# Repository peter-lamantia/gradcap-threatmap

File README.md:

# Graduation Cap Live Threat Map PCB

## About

This is a pet project to learn more about microcontroller development and PCB design.

My plan is to: 
1. Reverse engineer the Fortinet WebSocket API
2. Program an ESP32 to connect to said API and log messages to serial
3. Design a PCB with:
   - an ESP32-S3
   - a world map graphic and WS2812B LEDs placed at key cities
   - a lithium battery and charging circuit
   - dimensions that will place it neatly on a graduation cap
   - a display to show the attack details
4. Program the ESP32 to parse the incoming WebSocket such that:
   - the longitudinal data will map to the closest physical LED on the board
   - the LED will light up with a certain color depending on the threat type
   - ideally, I can make the LEDs animated in a cool way

## Roadmap
- WiFi connection reestablishment
- WebSocket connection reestablishment
- An actual PCB to mess around with. It may be useful to do this in revisions, e.g. make a PCB with the LEDs first, write the software for that, then make a more capable PCB with all components. After all, it is my first time doing this.
- Figure out how to actually debug (not just print program state to serial!)

## Changelog

### 2024-07-07
- Full migration to Platform.io (it's great!)
- Started printing out threats to an OLED display
   - Used the U8g2 library, specifically [u8log](https://github.com/olikraus/u8g2/wiki/u8logreference) for display output
   - Parsed the JSON sent from the WebSocket using [ArduinoJSON](https://arduinojson.org/)
- Added and did some testing with [FastLED](https://github.com/FastLED/FastLED), but have not implemented it yet (it is likely best to wait until I've made the PCB)

### 2024-06-29 (initial commit)
- WiFi connection establishment
- WebSocket connection to Fortinet
- Prints WebSocket messages to serial

## Known issues/fixes
- If serial is enabled, the XIAO ESP32-S3 will not allow reflashing. To fix this, hold the boot button while powering it on, and then flash at will!

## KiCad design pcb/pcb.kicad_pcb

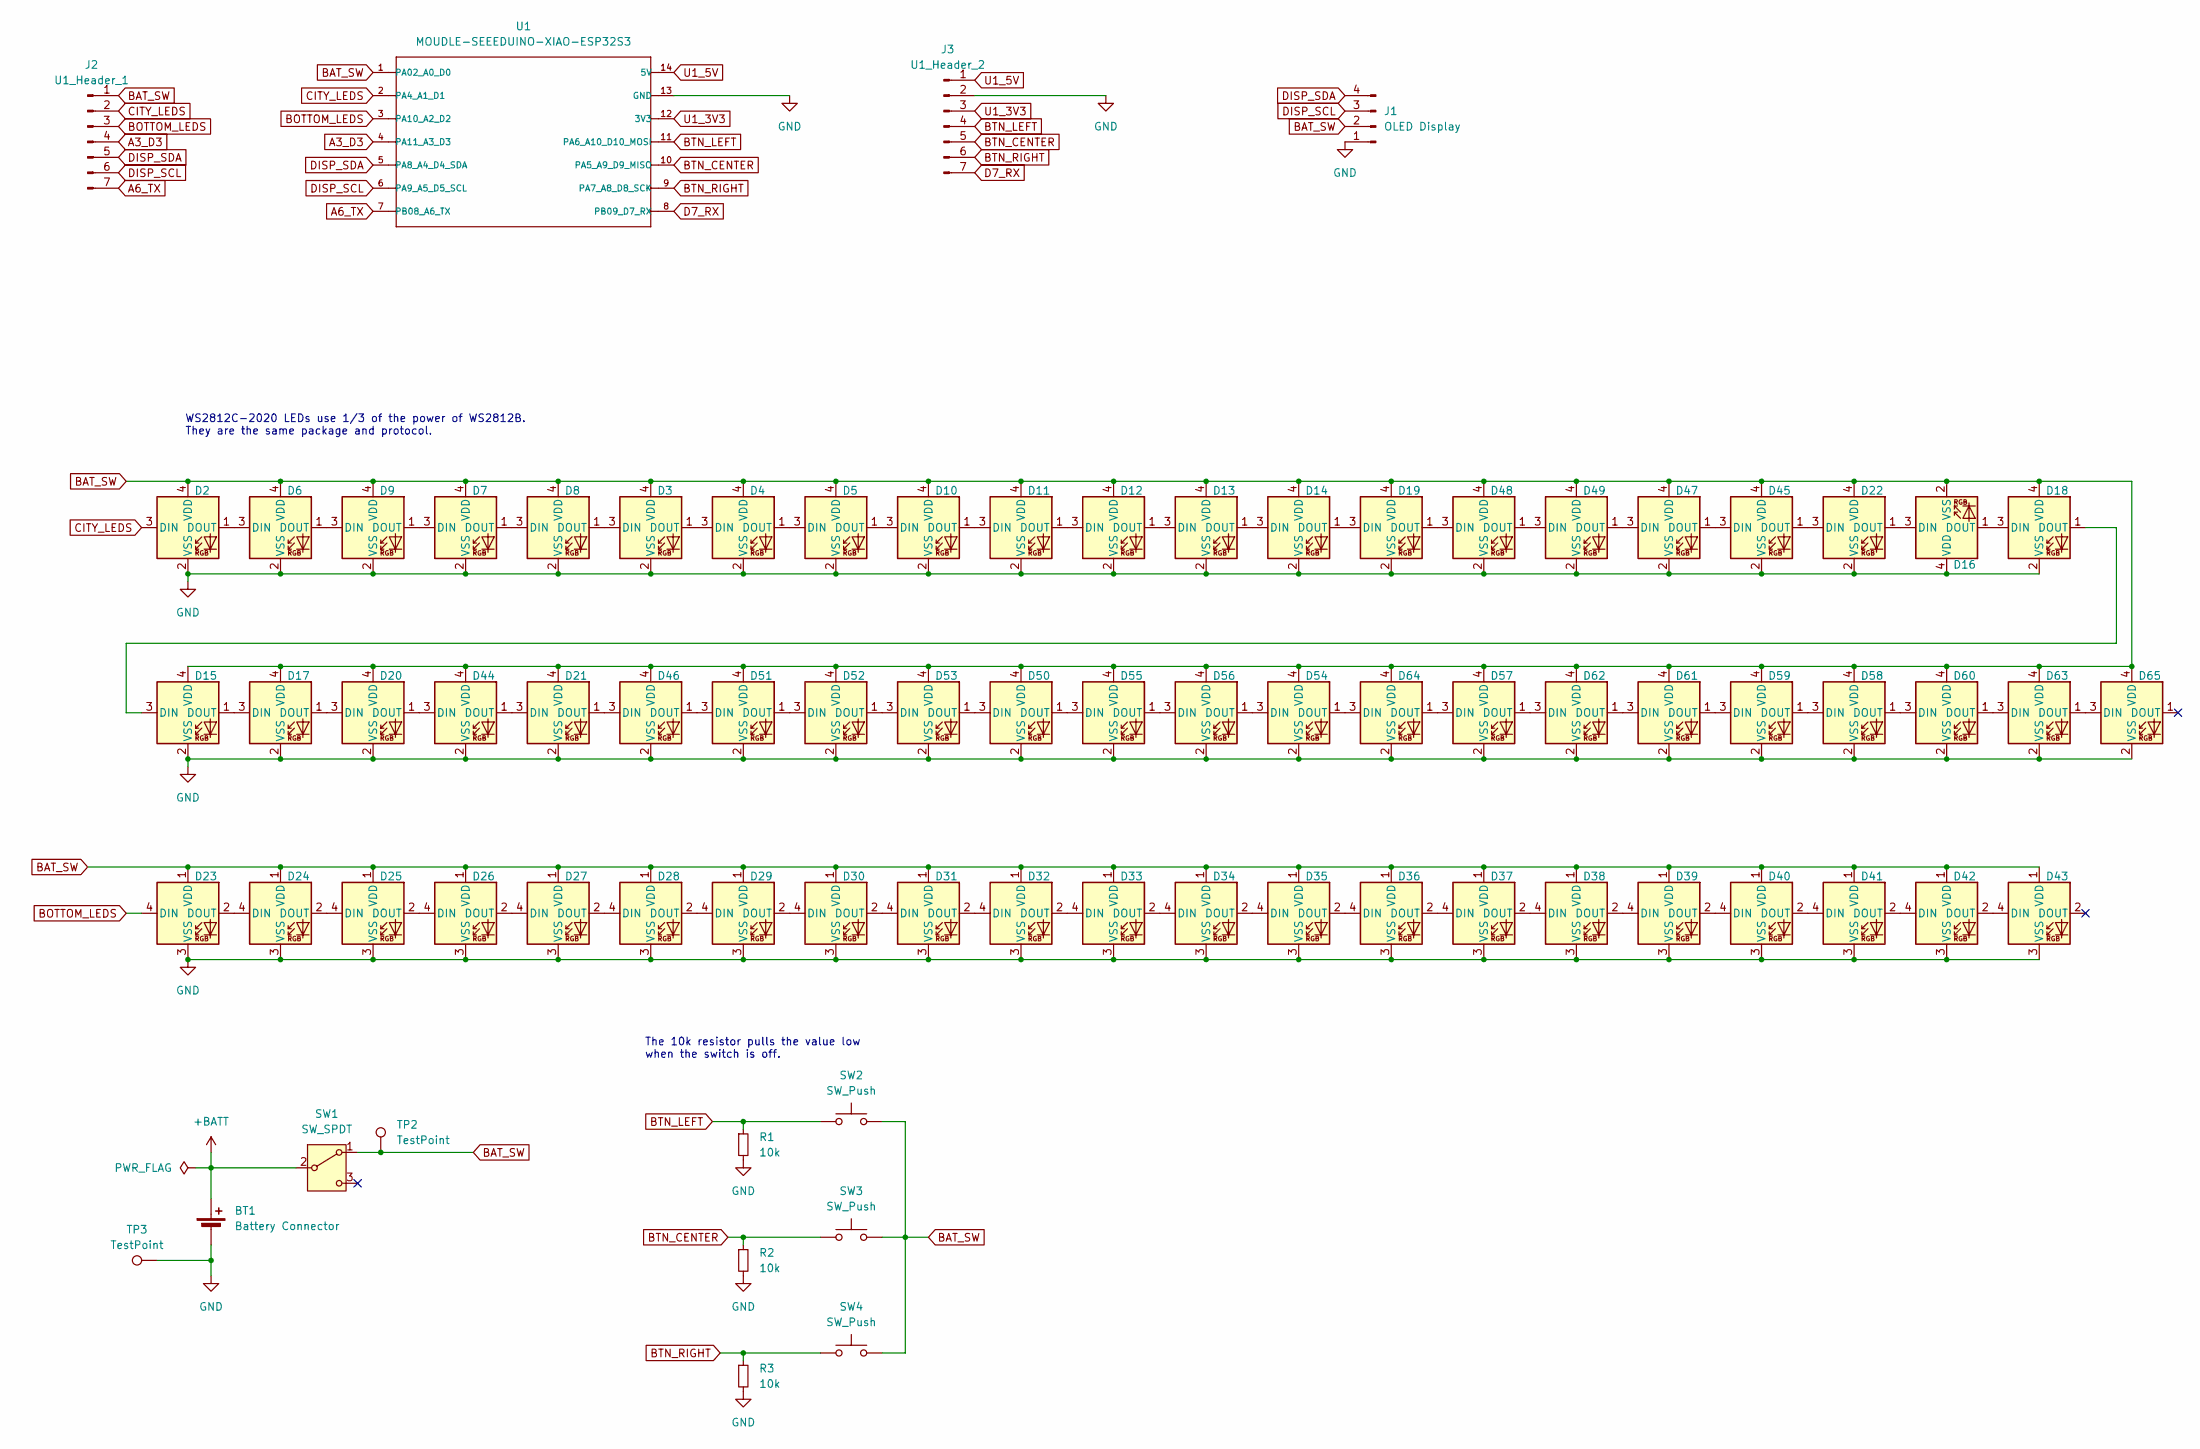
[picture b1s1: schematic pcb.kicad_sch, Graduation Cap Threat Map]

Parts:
BT1: Battery Connector; JST_PH_S2B-PH-K_1x02_P2.00mm_Horizontal
D2, D3, D4, D5, D6, D7, D8, D9, D10, D11, D12, D13, D14, D15, D16, D17, D18, D19, D20, D21, D22, D44, D45, D46, D47, D48, D49, D50, D51, D52, D53, D54, D55, D56, D57, D58, D59, D60, D61, D62, D63, D64, D65: WS2812C-2020; LED_WS2812B-2020_PLCC4_2.0x2.0mm
D23, D24, D25, D26, D27, D28, D29, D30, D31, D32, D33, D34, D35, D36, D37, D38, D39, D40, D41, D42, D43: WS2812C; LED_WS2812B_PLCC4_5.0x5.0mm_P3.2mm
J1: OLED Display; PinHeader_1x04_P2.54mm_Vertical
J2: U1_Header_1; PinSocket_1x07_P2.54mm_Vertical
J3: U1_Header_2; PinSocket_1x07_P2.54mm_Vertical
R1, R2, R3: 10k; R_Axial_DIN0207_L6.3mm_D2.5mm_P7.62mm_Horizontal
SW1: SW_SPDT; SW_Slide_SPDT_Angled_CK_OS102011MA1Q
SW2, SW3, SW4: SW_Push; SW_PUSH-12mm
TP2, TP3: TestPoint; TestPoint_Keystone_5015_Micro_Mini
U1: MOUDLE-SEEEDUINO-XIAO-ESP32S3; XIAO-ESP32S3-DIP

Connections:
+BATT: BT1.1 (+), SW1.2 (B)
A3_D3: J2.4, U1.4 (PA11_A3_D3)
A6_TX: J2.7, U1.7 (PB08_A6_TX)
BAT_SW: D2.4 (VDD), D3.4 (VDD), D4.4 (VDD), D5.4 (VDD), D6.4 (VDD), D7.4 (VDD), D8.4 (VDD), D9.4 (VDD), D10.4 (VDD), D11.4 (VDD), D12.4 (VDD), D13.4 (VDD), D14.4 (VDD), D15.4 (VDD), D16.2 (VSS), D17.4 (VDD), D18.4 (VDD), D19.4 (VDD), D20.4 (VDD), D21.4 (VDD), D22.4 (VDD), D23.1 (VDD), D24.1 (VDD), D25.1 (VDD), D26.1 (VDD), D27.1 (VDD), D28.1 (VDD), D29.1 (VDD), D30.1 (VDD), D31.1 (VDD), D32.1 (VDD), D33.1 (VDD), D34.1 (VDD), D35.1 (VDD), D36.1 (VDD), D37.1 (VDD), D38.1 (VDD), D39.1 (VDD), D40.1 (VDD), D41.1 (VDD), D42.1 (VDD), D43.1 (VDD), D44.4 (VDD), D45.4 (VDD), D46.4 (VDD), D47.4 (VDD), D48.4 (VDD), D49.4 (VDD), D50.4 (VDD), D51.4 (VDD), D52.4 (VDD), D53.4 (VDD), D54.4 (VDD), D55.4 (VDD), D56.4 (VDD), D57.4 (VDD), D58.4 (VDD), D59.4 (VDD), D60.4 (VDD), D61.4 (VDD), D62.4 (VDD), D63.4 (VDD), D64.4 (VDD), D65.4 (VDD), J1.2, J2.1, SW1.1 (A), SW2.2, SW3.2, SW4.2, TP2.1, U1.1 (PA02_A0_D0); also elsewhere on the board
BOTTOM_LEDS: D23.4 (DIN), J2.3, U1.3 (PA10_A2_D2)
BTN_CENTER: J3.5, R2.1, SW3.1, U1.10 (PA5_A9_D9_MISO)
BTN_LEFT: J3.4, R1.1, SW2.1, U1.11 (PA6_A10_D10_MOSI)
BTN_RIGHT: J3.6, R3.1, SW4.1, U1.9 (PA7_A8_D8_SCK)
CITY_LEDS: D2.3 (DIN), J2.2, U1.2 (PA4_A1_D1)
D7_RX: J3.7, U1.8 (PB09_D7_RX)
DISP_SCL: J1.3, J2.6, U1.6 (PA9_A5_D5_SCL)
DISP_SDA: J1.4, J2.5, U1.5 (PA8_A4_D4_SDA)
GND: BT1.2 (-), D2.2 (VSS), D3.2 (VSS), D4.2 (VSS), D5.2 (VSS), D6.2 (VSS), D7.2 (VSS), D8.2 (VSS), D9.2 (VSS), D10.2 (VSS), D11.2 (VSS), D12.2 (VSS), D13.2 (VSS), D14.2 (VSS), D15.2 (VSS), D16.4 (VDD), D17.2 (VSS), D18.2 (VSS), D19.2 (VSS), D20.2 (VSS), D21.2 (VSS), D22.2 (VSS), D23.3 (VSS), D24.3 (VSS), D25.3 (VSS), D26.3 (VSS), D27.3 (VSS), D28.3 (VSS), D29.3 (VSS), D30.3 (VSS), D31.3 (VSS), D32.3 (VSS), D33.3 (VSS), D34.3 (VSS), D35.3 (VSS), D36.3 (VSS), D37.3 (VSS), D38.3 (VSS), D39.3 (VSS), D40.3 (VSS), D41.3 (VSS), D42.3 (VSS), D43.3 (VSS), D44.2 (VSS), D45.2 (VSS), D46.2 (VSS), D47.2 (VSS), D48.2 (VSS), D49.2 (VSS), D50.2 (VSS), D51.2 (VSS), D52.2 (VSS), D53.2 (VSS), D54.2 (VSS), D55.2 (VSS), D56.2 (VSS), D57.2 (VSS), D58.2 (VSS), D59.2 (VSS), D60.2 (VSS), D61.2 (VSS), D62.2 (VSS), D63.2 (VSS), D64.2 (VSS), D65.2 (VSS), J1.1, J3.2, R1.2, R2.2, R3.2, TP3.1, U1.13 (GND); also elsewhere on the board
unnamed: D2.1 (DOUT), D6.3 (DIN)
unnamed: D3.3 (DIN), D8.1 (DOUT)
unnamed: D3.1 (DOUT), D4.3 (DIN)
unnamed: D4.1 (DOUT), D5.3 (DIN)
unnamed: D6.1 (DOUT), D9.3 (DIN)
unnamed: D7.3 (DIN), D9.1 (DOUT)
unnamed: D7.1 (DOUT), D8.3 (DIN)
unnamed: D5.1 (DOUT), D10.3 (DIN)
unnamed: D10.1 (DOUT), D11.3 (DIN)
unnamed: D11.1 (DOUT), D12.3 (DIN)
unnamed: D12.1 (DOUT), D13.3 (DIN)
unnamed: D13.1 (DOUT), D14.3 (DIN)
unnamed: D14.1 (DOUT), D19.3 (DIN)
unnamed: D15.3 (DIN), D18.1 (DOUT)
unnamed: D15.1 (DOUT), D17.3 (DIN)
unnamed: D16.3 (DIN), D22.1 (DOUT)
unnamed: D16.1 (DOUT), D18.3 (DIN)
unnamed: D17.1 (DOUT), D20.3 (DIN)
unnamed: D19.1 (DOUT), D48.3 (DIN)
unnamed: D20.1 (DOUT), D44.3 (DIN)
unnamed: D21.3 (DIN), D44.1 (DOUT)
unnamed: D21.1 (DOUT), D46.3 (DIN)
unnamed: D22.3 (DIN), D45.1 (DOUT)
unnamed: D23.2 (DOUT), D24.4 (DIN)
unnamed: D24.2 (DOUT), D25.4 (DIN)
unnamed: D25.2 (DOUT), D26.4 (DIN)
unnamed: D26.2 (DOUT), D27.4 (DIN)
unnamed: D27.2 (DOUT), D28.4 (DIN)
unnamed: D28.2 (DOUT), D29.4 (DIN)
unnamed: D29.2 (DOUT), D30.4 (DIN)
unnamed: D30.2 (DOUT), D31.4 (DIN)
unnamed: D31.2 (DOUT), D32.4 (DIN)
unnamed: D32.2 (DOUT), D33.4 (DIN)
unnamed: D33.2 (DOUT), D34.4 (DIN)
unnamed: D34.2 (DOUT), D35.4 (DIN)
unnamed: D35.2 (DOUT), D36.4 (DIN)
unnamed: D36.2 (DOUT), D37.4 (DIN)
unnamed: D37.2 (DOUT), D38.4 (DIN)
unnamed: D38.2 (DOUT), D39.4 (DIN)
unnamed: D39.2 (DOUT), D40.4 (DIN)
unnamed: D40.2 (DOUT), D41.4 (DIN)
unnamed: D41.2 (DOUT), D42.4 (DIN)
unnamed: D42.2 (DOUT), D43.4 (DIN)
unnamed: D45.3 (DIN), D47.1 (DOUT)
unnamed: D46.1 (DOUT), D51.3 (DIN)
unnamed: D47.3 (DIN), D49.1 (DOUT)
unnamed: D48.1 (DOUT), D49.3 (DIN)
unnamed: D50.3 (DIN), D53.1 (DOUT)
unnamed: D50.1 (DOUT), D55.3 (DIN)
unnamed: D51.1 (DOUT), D52.3 (DIN)
unnamed: D52.1 (DOUT), D53.3 (DIN)
unnamed: D54.3 (DIN), D56.1 (DOUT)
unnamed: D54.1 (DOUT), D64.3 (DIN)
unnamed: D55.1 (DOUT), D56.3 (DIN)
unnamed: D57.3 (DIN), D64.1 (DOUT)
unnamed: D57.1 (DOUT), D62.3 (DIN)
unnamed: D58.3 (DIN), D59.1 (DOUT)
unnamed: D58.1 (DOUT), D60.3 (DIN)
unnamed: D59.3 (DIN), D61.1 (DOUT)
unnamed: D60.1 (DOUT), D63.3 (DIN)
unnamed: D61.3 (DIN), D62.1 (DOUT)
unnamed: D63.1 (DOUT), D65.3 (DIN)
U1_3V3: J3.3, U1.12 (3V3)
U1_5V: J3.1, U1.14 (5V)

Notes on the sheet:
WS2812C-2020 LEDs use 1/3 of the power of WS2812B. They are the same package and protocol.
The 10k resistor pulls the value low when the switch is off.

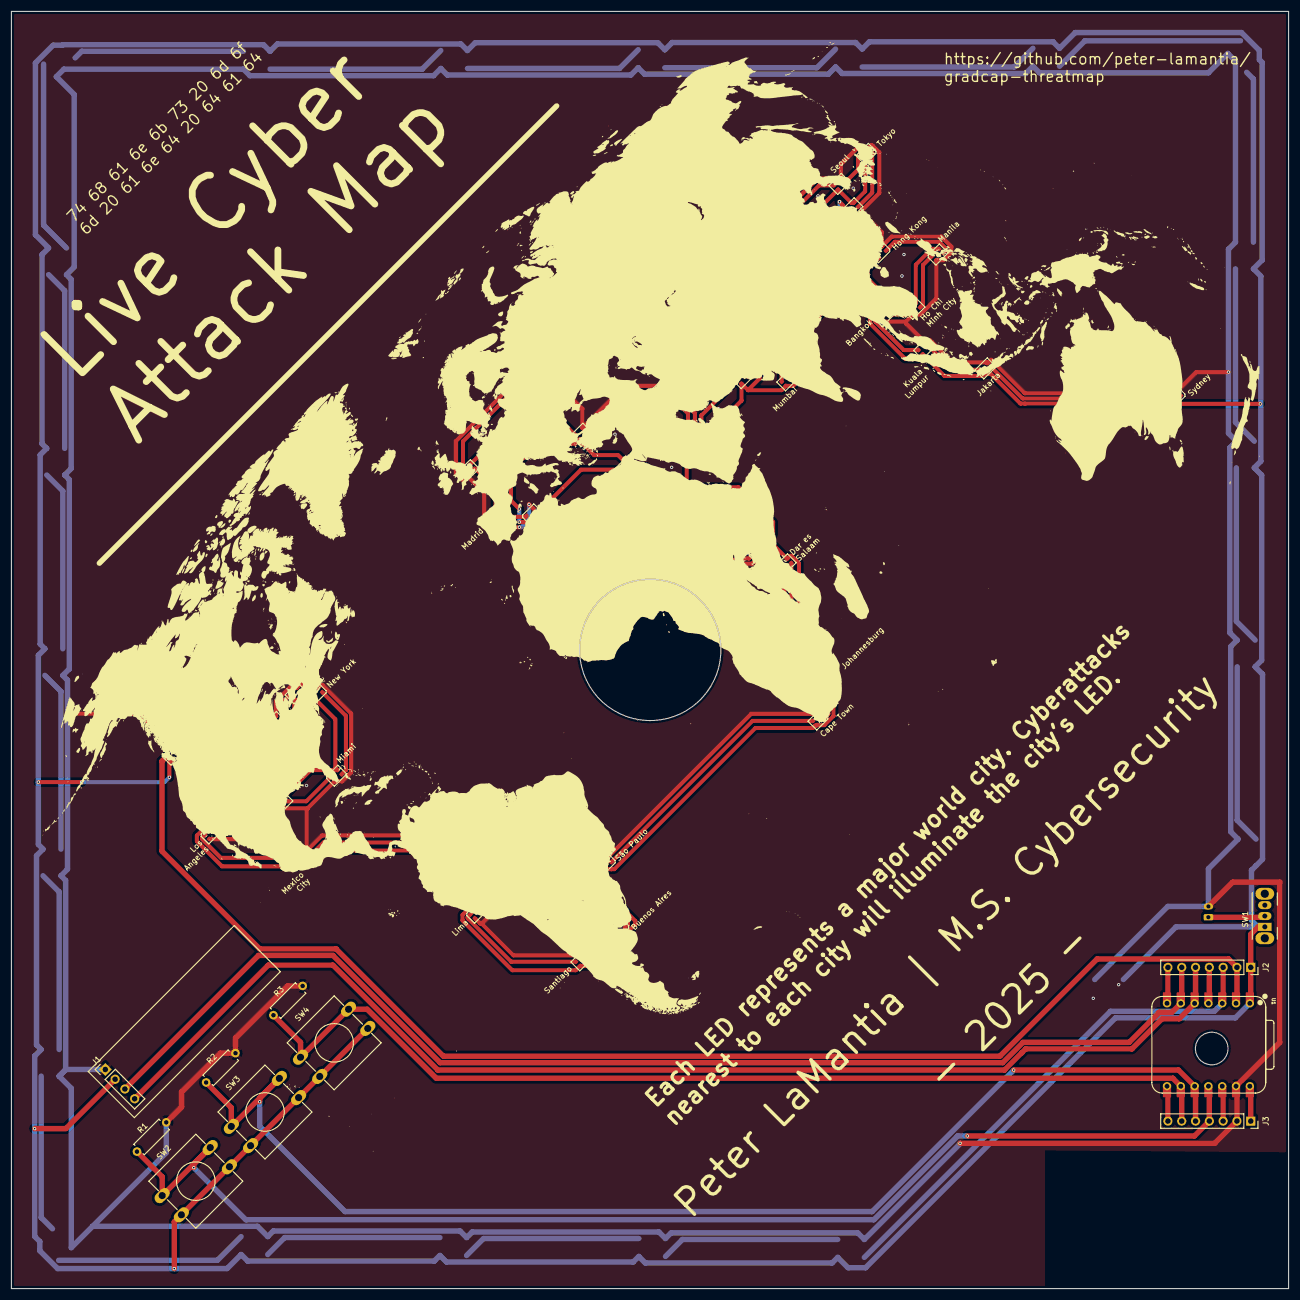
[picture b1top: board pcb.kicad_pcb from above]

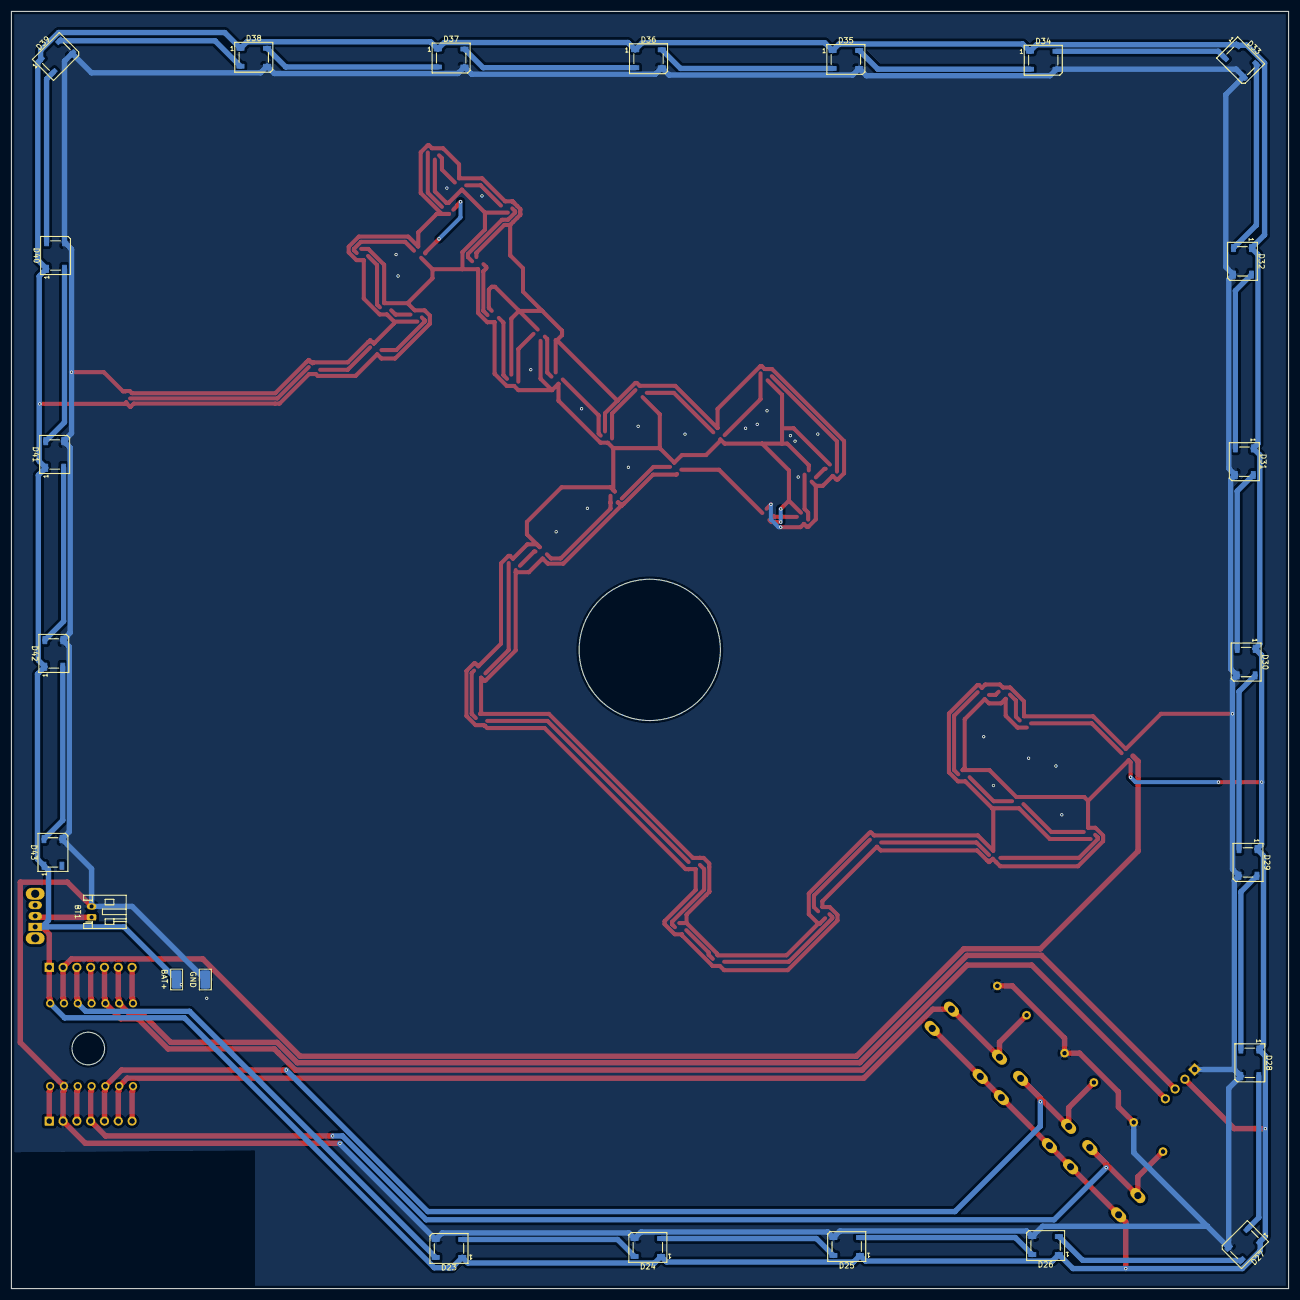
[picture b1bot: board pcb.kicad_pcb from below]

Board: 2 copper layers, 235.0 x 235.0 mm, 78 parts (24 on the bottom side), 77 nets.

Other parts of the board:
BAT+: TestPoint; TestPoint_Keystone_5015_Micro_Mini
GND: TestPoint; TestPoint_Keystone_5015_Micro_Mini

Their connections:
BAT_SW: BAT+.1; also elsewhere on the board
GND: GND.1; also elsewhere on the board

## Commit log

2024-07-08 Migration to Platform.io and OLED display output
2025-04-11 It's crunch time
    This probably has more files than I am supposed to commit to VCS
2025-04-15 Moving along
2025-04-16 Almost there
2025-05-12 Updated pcb
